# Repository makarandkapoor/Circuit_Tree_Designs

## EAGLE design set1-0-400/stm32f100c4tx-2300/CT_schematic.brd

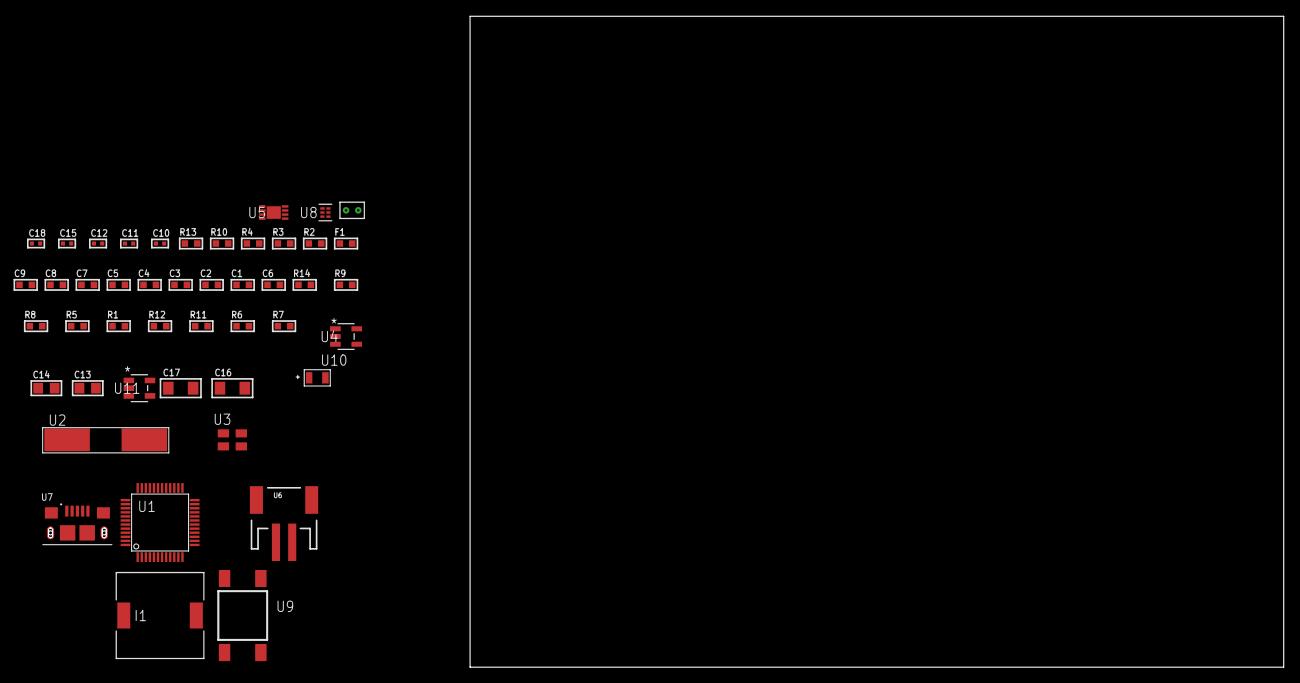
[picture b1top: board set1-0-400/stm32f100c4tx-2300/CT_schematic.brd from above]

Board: 2 copper layers, 151.8 x 80.0 mm, 46 parts (0 on the bottom side), 22 nets, no tracks yet.

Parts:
C1, C9: 1e-06; C0603
C2, C3, C4, C5: 1e-07; C0603
C6: 4.7e-06; C0603
C7, C8: 1e-08; C0603
C10, C11: 1e-11; C0402
C12, C18: 1e-08; C0402
C13, C14: 1e-05; C0805
C15: 1e-07; C0402
C16, C17: 1e-05; C1206
F1: 240.0; L0603
I1: 2.5e-06; DR1040
R1, R5, R8, R9, R14: 10000.0; R0603
R2: 1000.0; R0603
R3: 1600.5; R0603
R4: 4700.0; R0603
R6: 220000.0; R0603
R7: 1000000.0; R0603
R10: 9100.0; R0603
R11: 680000.0; R0603
R12: 120000.0; R0603
R13: 2000.0; R0603
U1: stm32f100c4t6; LQFP48
U2: ABLS-25.000MHZ-B2F-T
U3: ASEK-32.768KHz-ECST; ASEK
U4: ltc3406es5; TSOT-23-5
U5: MCP73831T-2ACI/MC; DFN8_2X3MC
U6: S2B-PH-SM4-TB(LF)(SN); JST-2-SMD
U7: 10118193-0001LF; FCI_10118193-0001LF
U8: TPS3895ADRYR; SON-6
U9: 4-1437565-2; SW_4-1437565-2
U10: Q65110A2395; LGM67K-G1J2-24-Z
U11: nc7sz125m5x; NC7SZ125M5X
U12: Dummy; DUMMY_PACKAGE_92

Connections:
CLK_CRYSTAL_U1_5: C10.1, U1.5, U2.1
CLK_CRYSTAL_U1_6: C11.1, U1.6, U2.2
CLK_U1_3: U1.3, U3.3
GND: C1.2, C2.2, C3.2, C4.2, C5.2, C6.2, C7.2, C8.2, C9.2, C10.2, C11.2, C12.2, C13.2, C14.1, C14.2, C15.2, C16.2, C17.2, C18.2, R2.2, R5.2, R6.2, R10.2, R12.2, R13.2, U1.8, U1.23, U1.35, U1.47, U3.2, U4.2, U5.6, U5.9, U6.2, U7.5, U7.6, U7.7, U7.8, U7.9, U8.2, U10.C, U11.1, U11.3, U12.1
INPUT_USBPOWER_5V: C16.1, R14.2, U5.1, U5.2, U7.1
NET_U1_7: R4.1, U1.7, U11.4
NET_U1_9: C7.1, C8.1, C9.1, F1.1, U1.9
NET_U1_44: R5.1, U1.44
NET_U1_45: R3.1, U1.45, U10.A
NET_U1_46: R1.1, U1.46, U9.3, U9.4
NET_U4_3: I1.1, U4.3
NET_U4_5: R6.1, R7.1, U4.5
NET_U4_ATNET_3: I1.2, R7.2
NET_U5_5: R14.1, U5.5
NET_U5_8: R13.1, U5.8
NET_U8_1: R9.1, R10.1, U8.1
NET_U8_3: R11.2, R12.1, U8.3
NET_U8_4: R8.1, U8.4, U11.2
NET_U9_1: R2.1, U9.1, U9.2
PROC_DAC_OUT2: U1.15, U12.2
VCC_S1_3V7: C13.1, C17.1, U4.4, U5.3, U5.4, U6.1
VCC_TIER1_3V3: C1.1, C2.1, C3.1, C4.1, C5.1, C6.1, C12.1, C14.2, C15.1, C18.1, F1.2, I1.2, R1.2, R3.2, R4.2, R7.2, R8.2, R9.2, R11.1, U1.1, U1.24, U1.36, U1.48, U3.4, U8.6, U11.5

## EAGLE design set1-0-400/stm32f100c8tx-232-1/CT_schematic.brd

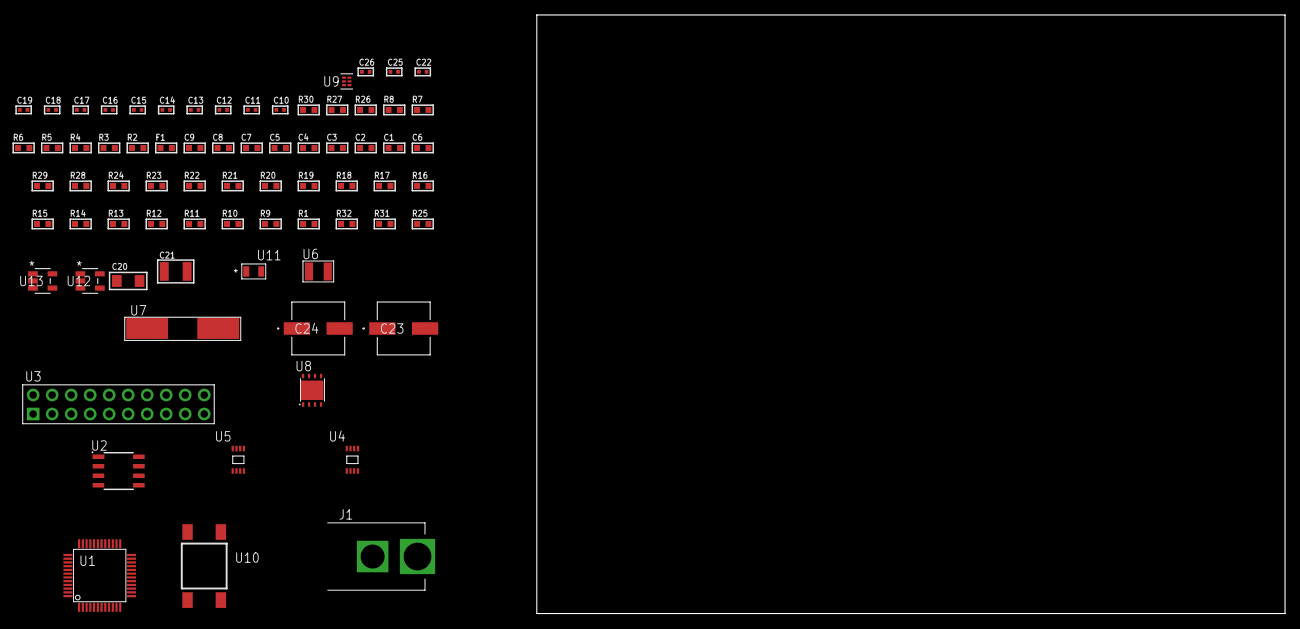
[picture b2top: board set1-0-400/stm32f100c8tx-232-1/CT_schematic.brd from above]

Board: 2 copper layers, 100.0 x 80.0 mm, 73 parts (0 on the bottom side), 42 nets, no tracks yet.

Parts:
C1, C9: 1e-06; C0603
C2, C3, C4, C5: 1e-07; C0603
C6: 4.7e-06; C0603
C7, C8: 1e-08; C0603
C10, C11, C12, C13: 1e-11; C0402
C14, C17, C18, C19, C25, C26: 1e-08; C0402
C15, C16, C22: 1e-07; C0402
C20: 1e-05; C1206
C21: 1e-05; C1210
C23, C24: 0.0001; EXV-9H
F1: 240.0; L0603
J1: PJ-037B; PJ-037B_PACKAGE
R1, R9, R10, R11, R12, R13, R14, R15, R16, R17, R18, R19, R20, R21, R22, R23, R24, R28, R29: 10000.0; R0603
R2, R27: 1000.0; R0603
R3: 1600.5; R0603
R4: 4700.0; R0603
R5, R6, R7, R8: 2200.0; R0603
R25: 100000.0; R0603
R26: 2231.0; R0603
R30: 9100.0; R0603
R31: 680000.0; R0603
R32: 120000.0; R0603
U1: stm32f100c8t7; LQFP48
U2: AT25020B-SSHL-T; SOIC-8
U3: TST-110-05-T-D-RA
U4, U5: 24AA128T-I/MNY; TDFN-8/6MM
U6: ABS07-32.768KHZ-7-T
U7: ABLS-25.000MHZ-B2F-T
U8: LP3878SDX-ADJ/NOPB; WSON-8
U9: TPS3895ADRYR; SON-6
U10: 4-1437565-2; SW_4-1437565-2
U11: Q65110A2395; LGM67K-G1J2-24-Z
U12, U13: nc7sz125m5x; NC7SZ125M5X

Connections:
CLK_CRYSTAL_U1_3: C10.1, U1.3, U6.1
CLK_CRYSTAL_U1_4: C11.1, U1.4, U6.2
CLK_CRYSTAL_U1_5: C12.1, U1.5, U7.1
CLK_CRYSTAL_U1_6: C13.1, U1.6, U7.2
GND: C1.2, C2.2, C3.2, C4.2, C5.2, C6.2, C7.2, C8.2, C9.2, C10.2, C11.2, C12.2, C13.2, C14.2, C15.2, C16.2, C17.2, C18.2, C19.2, C20.2, C21.2, C22.2, C23.2, C24.2, C25.2, C26.2, J1.2, R2.2, R9.2, R18.2, R20.2, R21.2, R23.2, R27.2, R30.2, R32.2, U1.8, U1.23, U1.35, U1.47, U2.4, U3.4, U3.6, U3.8, U3.10, U3.12, U3.14, U3.16, U3.18, U3.20, U4.4, U4.7, U5.4, U5.7, U8.3, U8.PAD, U9.2, U11.C, U12.2, U12.3, U13.1, U13.3
NET_U1_7: R4.1, U1.7, U13.4
NET_U1_9: C7.1, C8.1, C9.1, F1.1, U1.9
NET_U1_21: R7.1, U1.21, U5.6
NET_U1_22: R8.1, U1.22, U5.5
NET_U1_42: R5.1, U1.42, U4.6
NET_U1_43: R6.1, U1.43, U4.5
NET_U1_44: R9.1, U1.44
NET_U1_45: R3.1, U1.45, U11.A
NET_U1_46: R1.1, U1.46, U10.3, U10.4
NET_U2_3: R10.1, U2.3
NET_U2_7: R12.1, U2.7
NET_U3_3: R13.1, U3.3
NET_U3_7: R15.1, U3.7
NET_U3_9: R16.1, U3.9
NET_U3_19: R18.1, U3.19
NET_U4_1: R19.1, U4.1
NET_U4_2: R20.1, U4.2
NET_U4_3: R21.1, U4.3
NET_U5_1: R22.1, U5.1
NET_U5_2: R23.1, U5.2
NET_U5_3: R24.1, U5.3
NET_U8_1: C19.1, U8.1
NET_U8_6: R26.2, R27.1, U8.6
NET_U8_8: R25.1, U8.8
NET_U9_1: R29.1, R30.1, U9.1
NET_U9_3: R31.2, R32.1, U9.3
NET_U9_4: R28.1, U9.4, U12.4, U13.2
NET_U10_1: R2.1, U10.1, U10.2
PROC_SPI1_MISO: U1.16, U2.2
PROC_SPI1_MOSI: U1.17, U2.5
PROC_SPI1_NSS: R11.1, U1.14, U2.1
PROC_SPI1_SCK: U1.15, U2.6
PROC_SYS_JTDI: R14.1, U1.38, U3.5
PROC_SYS_JTDO_TRACESWO: U1.39, U3.13
RST_OUT_U3_SRESET_B: R17.1, U3.15, U12.1
VCC_S1_6V4: C20.1, C23.1, C24.1, J1.1, R25.2, U8.4
VCC_TIER1_3V3: C1.1, C2.1, C3.1, C4.1, C5.1, C6.1, C14.1, C15.1, C16.1, C17.1, C18.1, C21.1, C22.1, C25.1, C26.1, F1.2, R1.2, R3.2, R4.2, R5.2, R6.2, R7.2, R8.2, R10.2, R11.2, R12.2, R13.2, R14.2, R15.2, R16.2, R17.2, R19.2, R22.2, R24.2, R26.1, R28.2, R29.2, R31.1, U1.1, U1.24, U1.36, U1.48, U2.8, U3.1, U3.2, U4.8, U5.8, U8.5, U9.6, U12.5, U13.5

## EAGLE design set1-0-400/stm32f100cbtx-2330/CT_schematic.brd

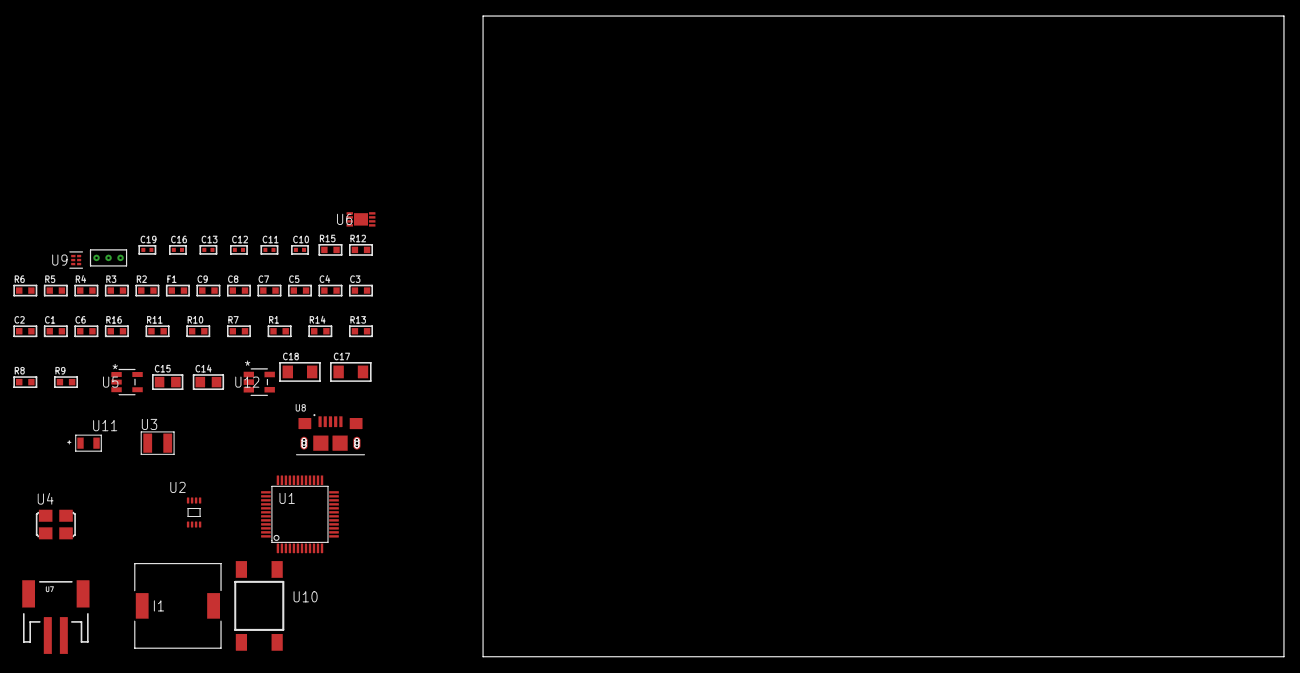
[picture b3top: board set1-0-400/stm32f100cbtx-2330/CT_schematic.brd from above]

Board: 2 copper layers, 122.6 x 80.0 mm, 50 parts (0 on the bottom side), 25 nets, no tracks yet.

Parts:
C1, C9: 1e-06; C0603
C2, C3, C4, C5: 1e-07; C0603
C6: 4.7e-06; C0603
C7, C8: 1e-08; C0603
C10, C11: 1e-11; C0402
C12, C13, C19: 1e-08; C0402
C14, C15: 1e-05; C0805
C16: 1e-07; C0402
C17, C18: 1e-05; C1206
F1: 240.0; L0603
I1: 2.5e-06; DR1040
R1, R7, R10, R11, R16: 10000.0; R0603
R2: 1000.0; R0603
R3: 1600.5; R0603
R4: 4700.0; R0603
R5, R6: 2200.0; R0603
R8: 220000.0; R0603
R9: 1000000.0; R0603
R12: 9100.0; R0603
R13: 680000.0; R0603
R14: 120000.0; R0603
R15: 2000.0; R0603
U1: stm32f100cbt7; LQFP48
U2: 24AA04-I/MC; TDFN-8/6MM
U3: ABS07-32.768KHZ-7-T
U4: ASFL1-25MHZ-NCS; ASFL1
U5: ltc3406es5; TSOT-23-5
U6: MCP73831T-2ACI/MC; DFN8_2X3MC
U7: S2B-PH-SM4-TB(LF)(SN); JST-2-SMD
U8: 10118193-0001LF; FCI_10118193-0001LF
U9: TPS3895ADRYR; SON-6
U10: 4-1437565-2; SW_4-1437565-2
U11: Q65110A2395; LGM67K-G1J2-24-Z
U12: nc7sz125m5x; NC7SZ125M5X
U13: Dummy; DUMMY_PACKAGE_103

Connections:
CLK_CRYSTAL_U1_3: C10.1, U1.3, U3.1
CLK_CRYSTAL_U1_4: C11.1, U1.4, U3.2
CLK_U1_5: U1.5, U4.3
GND: C1.2, C2.2, C3.2, C4.2, C5.2, C6.2, C7.2, C8.2, C9.2, C10.2, C11.2, C12.2, C13.2, C14.2, C15.1, C15.2, C16.2, C17.2, C18.2, C19.2, R2.2, R7.2, R8.2, R12.2, R14.2, R15.2, U1.8, U1.23, U1.35, U1.47, U2.4, U2.7, U4.2, U5.2, U6.6, U6.9, U7.2, U8.5, U8.6, U8.7, U8.8, U8.9, U9.2, U11.C, U12.1, U12.3, U13.1
INPUT_USBPOWER_5V: C17.1, R16.2, U6.1, U6.2, U8.1
NET_U1_7: R4.1, U1.7, U12.4
NET_U1_9: C7.1, C8.1, C9.1, F1.1, U1.9
NET_U1_42: R5.1, U1.42, U2.6
NET_U1_43: R6.1, U1.43, U2.5
NET_U1_44: R7.1, U1.44
NET_U1_45: R3.1, U1.45, U11.A
NET_U1_46: R1.1, U1.46, U10.3, U10.4
NET_U5_3: I1.1, U5.3
NET_U5_5: R8.1, R9.1, U5.5
NET_U5_ATNET_3: I1.2, R9.2
NET_U6_5: R16.1, U6.5
NET_U6_8: R15.1, U6.8
NET_U9_1: R11.1, R12.1, U9.1
NET_U9_3: R13.2, R14.1, U9.3
NET_U9_4: R10.1, U9.4, U12.2
NET_U10_1: R2.1, U10.1, U10.2
PROC_PC13_TAMPER_RTC: U1.2, U13.2
PROC_PD1_OSC_OUT: U1.6, U13.3
VCC_S1_3V7: C14.1, C18.1, U5.4, U6.3, U6.4, U7.1
VCC_TIER1_3V3: C1.1, C2.1, C3.1, C4.1, C5.1, C6.1, C12.1, C13.1, C15.2, C16.1, C19.1, F1.2, I1.2, R1.2, R3.2, R4.2, R5.2, R6.2, R9.2, R10.2, R11.2, R13.1, U1.1, U1.24, U1.36, U1.48, U2.8, U4.4, U9.6, U12.5

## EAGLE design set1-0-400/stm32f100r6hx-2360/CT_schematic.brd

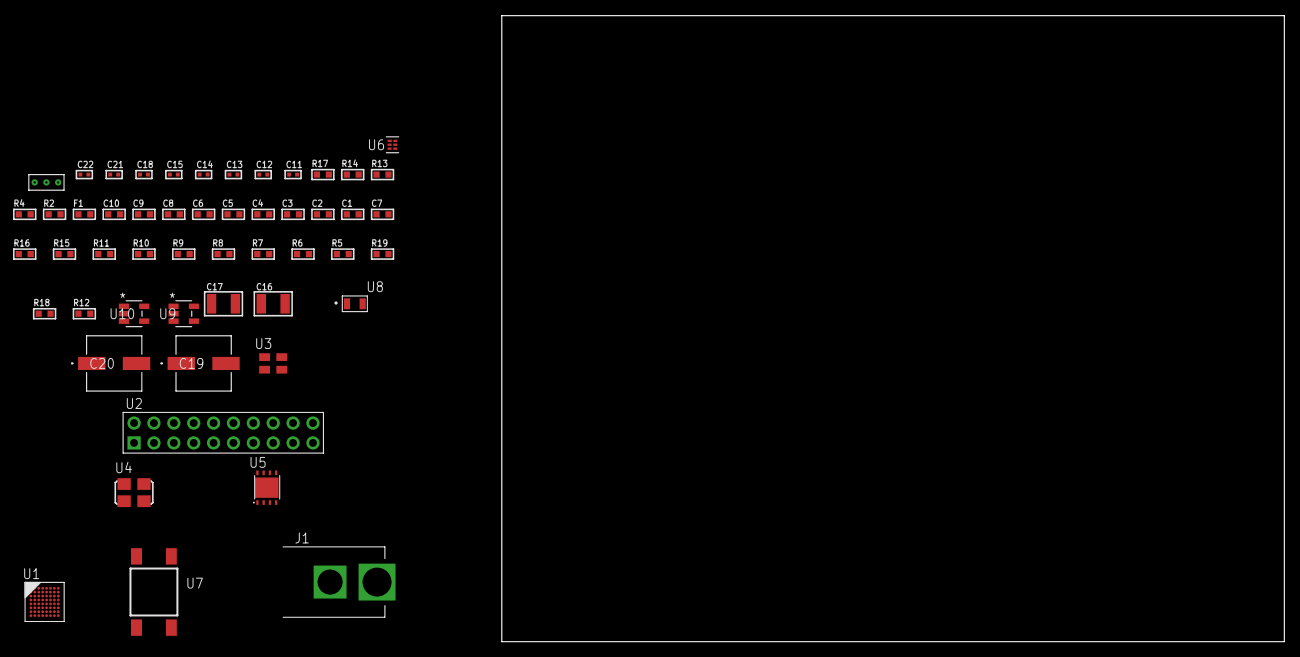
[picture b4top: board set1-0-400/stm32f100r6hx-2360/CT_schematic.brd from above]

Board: 2 copper layers, 100.0 x 80.0 mm, 52 parts (0 on the bottom side), 25 nets, no tracks yet.

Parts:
C1, C10: 1e-06; C0603
C2, C3, C4, C5, C6: 1e-07; C0603
C7: 4.7e-06; C0603
C8, C9: 1e-08; C0603
C11, C12, C18: 1e-07; C0402
C13, C14, C15, C21, C22: 1e-08; C0402
C16, C17: 1e-05; C1210
C19, C20: 0.0001; EXV-9H
F1: 240.0; L0603
J1: PJ-037B; PJ-037B_PACKAGE
R2, R14: 1000.0; R0603
R4: 4700.0; R0603
R5, R6, R7, R8, R9, R10, R11, R15, R16: 10000.0; R0603
R12: 100000.0; R0603
R13: 2231.0; R0603
R17: 9100.0; R0603
R18: 680000.0; R0603
R19: 120000.0; R0603
U1: stm32f100r6h6; TFBGA64
U2: TST-110-05-T-D-RA
U3: ASEK-32.768KHz-ECST; ASEK
U4: ASFL1-25MHZ-NCS; ASFL1
U5: LP3878SDX-ADJ/NOPB; WSON-8
U6: TPS3895ADRYR; SON-6
U7: 4-1437565-2; SW_4-1437565-2
U8: Q65110A2395; LGM67K-G1J2-24-Z
U9, U10: nc7sz125m5x; NC7SZ125M5X
U11: Dummy; DUMMY_PACKAGE_110

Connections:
CLK_U1_A1: U1.A1, U3.3
CLK_U1_C1: U1.C1, U4.3
GND: C1.2, C2.2, C3.2, C4.2, C5.2, C6.2, C7.2, C8.2, C9.2, C10.2, C11.2, C12.2, C13.2, C14.2, C15.2, C16.2, C17.2, C18.2, C19.2, C20.2, C21.2, C22.2, J1.2, R2.2, R5.2, R11.2, R14.2, R17.2, R19.2, U1.C2, U1.D4, U1.D5, U1.D6, U1.F1, U2.4, U2.6, U2.8, U2.10, U2.12, U2.14, U2.16, U2.18, U2.20, U3.2, U4.2, U5.3, U5.PAD, U6.2, U8.C, U9.2, U9.3, U10.1, U10.3, U11.1
NET_U1_B4: R5.1, U1.B4
NET_U1_E1: R4.1, U1.E1, U10.4
NET_U1_H1: C8.1, C9.1, C10.1, F1.1, U1.G1, U1.H1
NET_U1_H8: U7.3, U7.4
NET_U2_3: R6.1, U2.3
NET_U2_7: R8.1, U2.7
NET_U2_9: R9.1, U2.9
NET_U2_19: R11.1, U2.19
NET_U5_1: C15.1, U5.1
NET_U5_6: R13.2, R14.1, U5.6
NET_U5_8: R12.1, U5.8
NET_U6_1: R16.1, R17.1, U6.1
NET_U6_3: R18.2, R19.1, U6.3
NET_U6_4: R15.1, U6.4, U9.4, U10.2
NET_U7_1: R2.1, U7.1, U7.2
PROC_SYS_JTDI: R7.1, U1.A6, U2.5
PROC_SYS_JTDO_TRACESWO: U1.A5, U2.13
PROC_TIM1_CH2: U1.C7, U11.3
PROC_TIM1_CH4: U1.C8, U11.2
RST_OUT_U2_SRESET_B: R10.1, U2.15, U9.1
VCC_S1_15V8: C16.1, C19.1, C20.1, J1.1, R12.2, U5.4
VCC_TIER1_3V3: C1.1, C2.1, C3.1, C4.1, C5.1, C6.1, C7.1, C11.1, C12.1, C13.1, C14.1, C17.1, C18.1, C21.1, C22.1, F1.2, R4.2, R6.2, R7.2, R8.2, R9.2, R10.2, R13.1, R15.2, R16.2, R18.1, U1.B2, U1.D2, U1.E4, U1.E5, U1.E6, U2.1, U2.2, U3.4, U4.4, U5.5, U6.6, U9.5, U10.5

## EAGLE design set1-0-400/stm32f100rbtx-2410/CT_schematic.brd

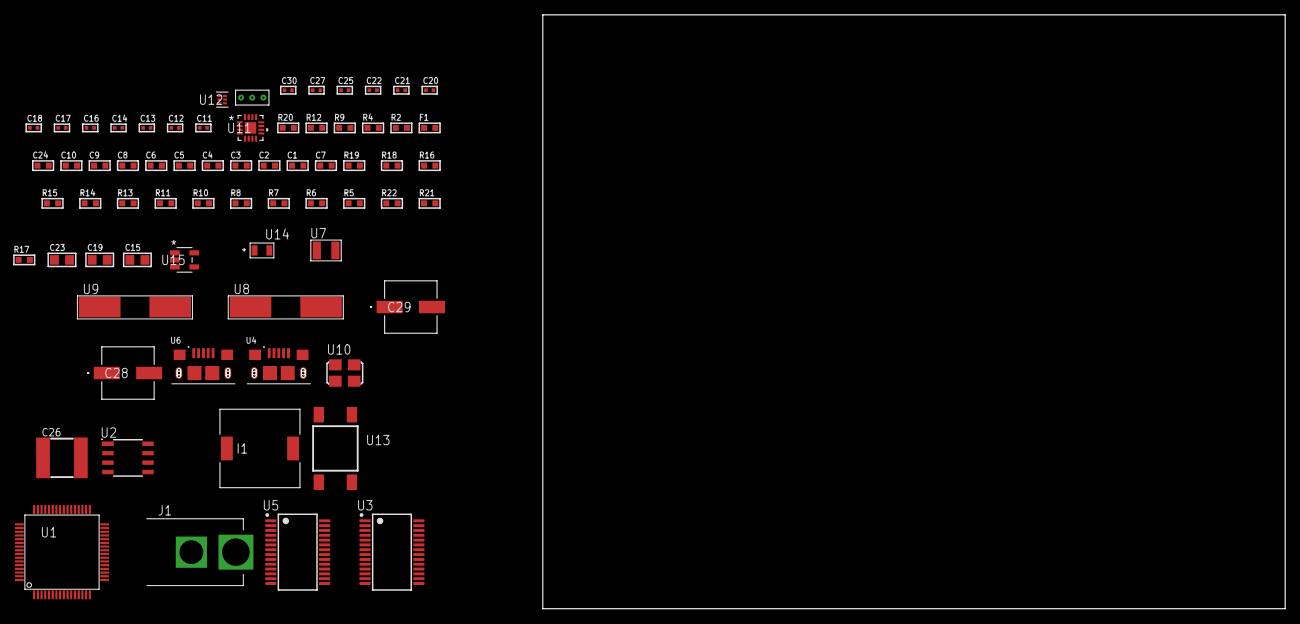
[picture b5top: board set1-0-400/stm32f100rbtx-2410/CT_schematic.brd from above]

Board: 2 copper layers, 69 parts (0 on the bottom side), 52 nets, no tracks yet.

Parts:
C1, C10, C24: 1e-06; C0603
C2, C3, C4, C5, C6: 1e-07; C0603
C7: 4.7e-06; C0603
C8, C9: 1e-08; C0603
C11, C12: 1e-11; C0402
C13, C22, C30: 1e-08; C0402
C14, C16, C17, C18, C20, C21, C25, C27: 1e-07; C0402
C15, C19: 4.7e-06; C0805
C23: 1e-05; C0805
C26: 6.8e-05; 2220
C28, C29: 0.0001; EXV-9H
F1: 240.0; L0603
I1: 3.8e-06; DR1040
J1: PJ-037B; PJ-037B_PACKAGE
R2: 1000.0; R0603
R4, R9, R12: 4700.0; R0603
R5, R6, R7, R8, R10, R11, R13, R14, R18, R19: 10000.0; R0603
R15: 20000.0; R0603
R16: 91000.0; R0603
R17: 300000.0; R0603
R20: 9100.0; R0603
R21: 680000.0; R0603
R22: 120000.0; R0603
U1: stm32f100rbt7; LQFP64
U2: AT25080B-SSHL-T; SOIC-8
U3, U5: FT232RL-REEL; SSOP-28
U4, U6: 10118193-0001LF; FCI_10118193-0001LF
U7: ABS07-32.768KHZ-7-T
U8, U9: ABLS-12.000MHZ-B4-T
U10: ASFL1-25MHZ-NCS; ASFL1
U11: LTC3601EUD#PBF; QFN-16_EP
U12: TPS3895ADRYR; SON-6
U13: 4-1437565-2; SW_4-1437565-2
U14: Q65110A2395; LGM67K-G1J2-24-Z
U15: nc7sz125m5x; NC7SZ125M5X
U16: Dummy; DUMMY_PACKAGE_143

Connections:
CLK_CRYSTAL_U1_3: C11.1, U1.3, U7.1
CLK_CRYSTAL_U1_4: C12.1, U1.4, U7.2
CLK_CRYSTAL_U3_27: U3.27, U8.1
CLK_CRYSTAL_U3_28: U3.28, U8.2
CLK_CRYSTAL_U5_27: U5.27, U9.1
CLK_CRYSTAL_U5_28: U5.28, U9.2
CLK_U1_5: U1.5, U10.3
GND: C1.2, C2.2, C3.2, C4.2, C5.2, C6.2, C7.2, C8.2, C9.2, C10.2, C11.2, C12.2, C13.2, C14.2, C15.2, C16.2, C17.2, C18.2, C19.2, C20.2, C21.2, C22.2, C23.2, C24.2, C26.1, C26.2, C27.2, C28.2, C29.2, C30.2, J1.2, R2.2, R5.2, R11.2, R14.2, R15.2, R17.2, R20.2, R22.2, U1.12, U1.18, U1.31, U1.47, U1.63, U2.4, U3.7, U3.18, U3.21, U3.25, U3.26, U4.5, U4.6, U4.7, U4.8, U4.9, U5.7, U5.18, U5.21, U5.25, U5.26, U6.5, U6.6, U6.7, U6.8, U6.9, U10.2, U11.1, U11.9, U11.17, U12.2, U14.C, U15.1, U15.3, U16.1
NET_U1_7: R4.1, U1.7, U15.4
NET_U1_13: C8.1, C9.1, C10.1, F1.1, U1.13
NET_U1_60: R5.1, U1.60
NET_U1_62: U13.3, U13.4
NET_U2_3: R6.1, U2.3
NET_U2_7: R8.1, U2.7
NET_U3_14: R10.1, U3.14
NET_U3_17: C16.1, U3.17
NET_U3_19: R11.1, U3.19
NET_U4_1: R9.1, U4.1
NET_U4_2: U3.16, U4.2
NET_U4_3: U3.15, U4.3
NET_U5_14: R13.1, U5.14
NET_U5_17: C20.1, U5.17
NET_U5_19: R14.1, U5.19
NET_U6_1: R12.1, U6.1
NET_U6_2: U5.16, U6.2
NET_U6_3: U5.15, U6.3
NET_U11_3: C25.2, I1.1, U11.3, U11.4
NET_U11_6: C25.1, U11.6
NET_U11_7: C24.1, U11.7, U11.12
NET_U11_10: R17.1, U11.10
NET_U11_11: R15.1, R16.1, U11.11
NET_U11_ATNET_3: I1.2, R16.2
NET_U12_1: R19.1, R20.1, U12.1
NET_U12_3: R21.2, R22.1, U12.3
NET_U12_4: R18.1, U12.4, U15.2
NET_U13_1: R2.1, U13.1, U13.2
PROC_PC13_TAMPER_RTC: U1.2, U16.2
PROC_PD1_OSC_OUT: U1.6, U16.3
PROC_SPI1_MISO: U1.22, U2.2
PROC_SPI1_MOSI: U1.23, U2.5
PROC_SPI1_NSS: R7.1, U1.20, U2.1
PROC_SPI1_SCK: U1.21, U2.6
PROC_USART1_CTS: U1.44, U3.3
PROC_USART1_RTS: U1.45, U3.11
PROC_USART1_RX: U1.43, U3.1
PROC_USART1_TX: U1.42, U3.5
PROC_USART2_CTS: U1.14, U5.3
PROC_USART2_RTS: U1.15, U5.11
PROC_USART2_RX: U1.17, U5.1
PROC_USART2_TX: U1.16, U5.5
VCC_S1_6V0: C23.1, C28.1, C29.1, J1.1, U11.15, U11.16
VCC_TIER1_3V3: C1.1, C2.1, C3.1, C4.1, C5.1, C6.1, C7.1, C13.1, C14.1, C15.1, C17.1, C18.1, C19.1, C21.1, C22.1, C26.2, C27.1, C30.1, F1.2, I1.2, R4.2, R6.2, R7.2, R8.2, R10.2, R13.2, R16.2, R18.2, R19.2, R21.1, U1.1, U1.19, U1.32, U1.48, U1.64, U2.8, U3.4, U3.20, U5.4, U5.20, U10.4, U11.8, U12.6, U15.5

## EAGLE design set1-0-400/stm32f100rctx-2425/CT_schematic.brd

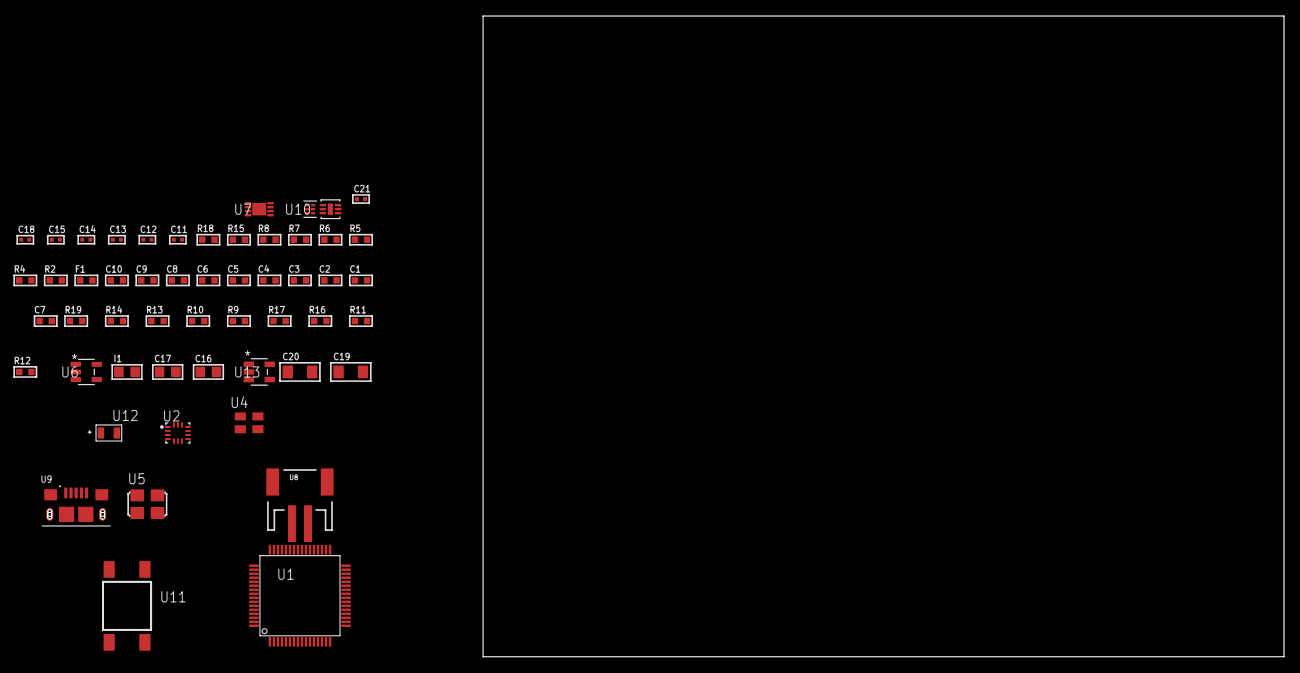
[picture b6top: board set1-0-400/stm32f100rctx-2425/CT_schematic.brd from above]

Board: 2 copper layers, 154.3 x 80.0 mm, 53 parts (0 on the bottom side), 25 nets, no tracks yet.

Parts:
C1, C10: 1e-06; C0603
C2, C3, C4, C5, C6: 1e-07; C0603
C7: 4.7e-06; C0603
C8, C9: 1e-08; C0603
C11, C12, C13, C18: 1e-07; C0402
C14, C15, C21: 1e-08; C0402
C16, C17: 1e-05; C0805
C19, C20: 1e-05; C1206
F1: 240.0; L0603
I1: 2.2e-06; L0805
R2: 1000.0; R0603
R4: 4700.0; R0603
R5, R6, R7, R8: 2200.0; R0603
R9, R10, R13, R14, R19: 10000.0; R0603
R11: 220000.0; R0603
R12: 1000000.0; R0603
R15: 9100.0; R0603
R16: 680000.0; R0603
R17: 120000.0; R0603
R18: 2000.0; R0603
U1: stm32f100rct7; LQFP64
U2: BMG250; LGA-14
U3: SI7006-A20-IM; DFN-6
U4: ASEK-32.768KHz-ECST; ASEK
U5: ASFL1-25MHZ-NCS; ASFL1
U6: ltc3406es5; TSOT-23-5
U7: MCP73831T-2ACI/MC; DFN8_2X3MC
U8: S2B-PH-SM4-TB(LF)(SN); JST-2-SMD
U9: 10118193-0001LF; FCI_10118193-0001LF
U10: TPS3895ADRYR; SON-6
U11: 4-1437565-2; SW_4-1437565-2
U12: Q65110A2395; LGM67K-G1J2-24-Z
U13: nc7sz125m5x; NC7SZ125M5X

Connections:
CLK_U1_3: U1.3, U4.3
CLK_U1_5: U1.5, U5.3
GND: C1.2, C2.2, C3.2, C4.2, C5.2, C6.2, C7.2, C8.2, C9.2, C10.2, C11.2, C12.2, C13.2, C14.2, C15.2, C16.2, C17.1, C17.2, C18.2, C19.2, C20.2, C21.2, R2.2, R9.2, R11.2, R15.2, R17.2, R18.2, U1.12, U1.18, U1.31, U1.47, U1.63, U2.1, U2.6, U2.7, U3.2, U3.7, U4.2, U5.2, U6.2, U7.6, U7.9, U8.2, U9.5, U9.6, U9.7, U9.8, U9.9, U10.2, U12.C, U13.1, U13.3
INPUT_USBPOWER_5V: C19.1, R19.2, U7.1, U7.2, U9.1
NET_U1_7: R4.1, U1.7, U13.4
NET_U1_13: C8.1, C9.1, C10.1, F1.1, U1.13
NET_U1_29: R7.1, U1.29, U2.13
NET_U1_30: R8.1, U1.30, U2.14
NET_U1_58: R5.1, U1.58, U3.6
NET_U1_59: R6.1, U1.59, U3.1
NET_U1_60: R9.1, U1.60
NET_U1_62: U11.3, U11.4
NET_U2_12: R10.1, U2.12
NET_U6_3: I1.1, U6.3
NET_U6_5: R11.1, R12.1, U6.5
NET_U6_ATNET_3: I1.2, R12.2
NET_U7_5: R19.1, U7.5
NET_U7_8: R18.1, U7.8
NET_U10_1: R14.1, R15.1, U10.1
NET_U10_3: R16.2, R17.1, U10.3
NET_U10_4: R13.1, U10.4, U13.2
NET_U11_1: R2.1, U11.1, U11.2
PROC_GPIO_TO_U2_INT1: U1.2, U2.4
VCC_S1_3V7: C16.1, C20.1, U6.4, U7.3, U7.4, U8.1
VCC_TIER1_3V3: C1.1, C2.1, C3.1, C4.1, C5.1, C6.1, C7.1, C11.1, C12.1, C13.1, C14.1, C15.1, C17.2, C18.1, C21.1, F1.2, I1.2, R4.2, R5.2, R6.2, R7.2, R8.2, R10.2, R12.2, R13.2, R14.2, R16.1, U1.1, U1.19, U1.32, U1.48, U1.64, U2.5, U2.8, U3.5, U4.4, U5.4, U10.6, U13.5

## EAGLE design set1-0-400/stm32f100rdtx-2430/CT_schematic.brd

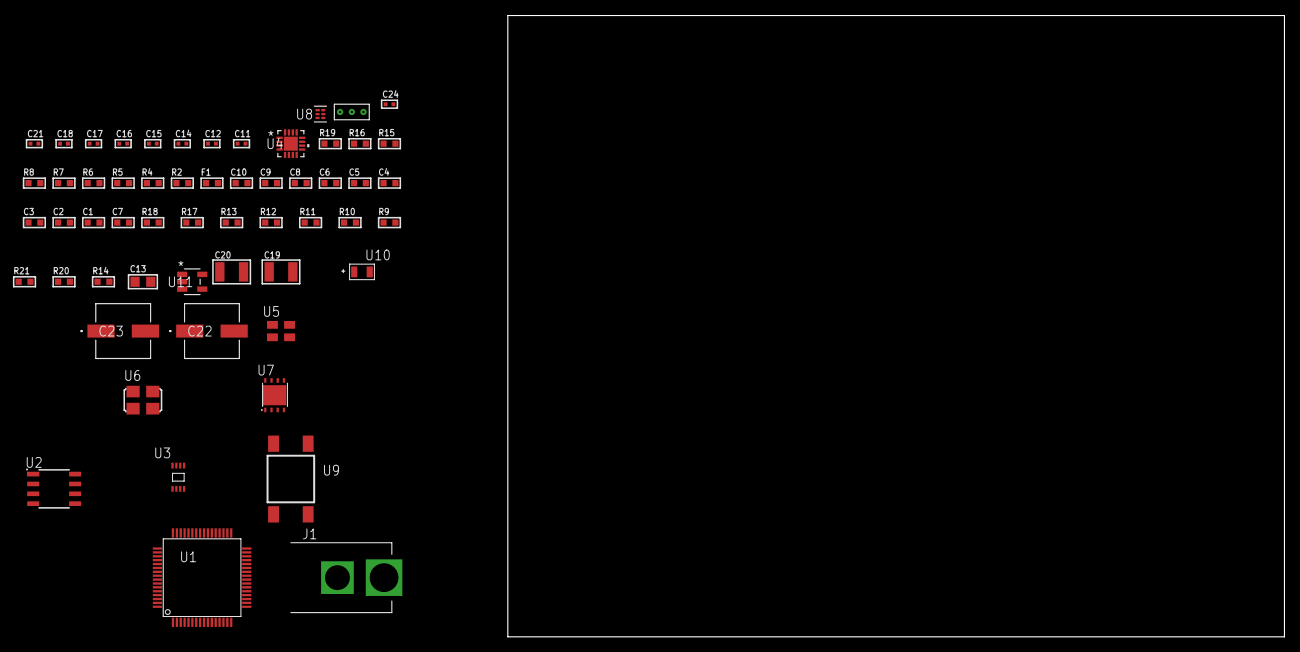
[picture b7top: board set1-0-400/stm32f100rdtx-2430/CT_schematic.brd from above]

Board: 2 copper layers, 100.0 x 80.0 mm, 57 parts (0 on the bottom side), 30 nets, no tracks yet.

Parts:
C1, C10: 1e-06; C0603
C2, C3, C4, C5, C6: 1e-07; C0603
C7: 4.7e-06; C0603
C8, C9: 1e-08; C0603
C11, C12, C16, C17, C18, C24: 1e-08; C0402
C13: 4.7e-06; C0805
C14, C15, C21: 1e-07; C0402
C19, C20: 1e-05; C1210
C22, C23: 0.0001; EXV-9H
F1: 240.0; L0603
J1: PJ-037B; PJ-037B_PACKAGE
R2, R16: 1000.0; R0603
R4: 4700.0; R0603
R5, R6, R7, R8: 2200.0; R0603
R9, R10, R11, R12, R13, R17, R18: 10000.0; R0603
R14: 100000.0; R0603
R15: 2231.0; R0603
R19: 9100.0; R0603
R20: 680000.0; R0603
R21: 120000.0; R0603
U1: stm32f100rdt6; LQFP64
U2: AT25080B-SSHL-T; SOIC-8
U3: 24AA02T-I/MNY; TDFN-8/6MM
U4: MMA8451QT; QFN-16
U5: ASEK-32.768KHz-ECST; ASEK
U6: ASFL1-25MHZ-NCS; ASFL1
U7: LP3878SDX-ADJ/NOPB; WSON-8
U8: TPS3895ADRYR; SON-6
U9: 4-1437565-2; SW_4-1437565-2
U10: Q65110A2395; LGM67K-G1J2-24-Z
U11: nc7sz125m5x; NC7SZ125M5X
U12: Dummy; DUMMY_PACKAGE_126

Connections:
CLK_U1_3: U1.3, U5.3
CLK_U1_5: U1.5, U6.3
GND: C1.2, C2.2, C3.2, C4.2, C5.2, C6.2, C7.2, C8.2, C9.2, C10.2, C11.2, C12.2, C13.2, C14.2, C15.2, C16.2, C17.2, C18.2, C19.2, C20.2, C21.2, C22.2, C23.2, C24.2, J1.2, R2.2, R9.2, R16.2, R19.2, R21.2, U1.12, U1.18, U1.31, U1.47, U1.63, U2.4, U3.4, U4.5, U4.10, U4.12, U4.17, U5.2, U6.2, U7.3, U7.PAD, U8.2, U10.C, U11.1, U11.3, U12.1
NET_U1_7: R4.1, U1.7, U11.4
NET_U1_13: C8.1, C9.1, C10.1, F1.1, U1.13
NET_U1_29: R7.1, U1.29, U3.6
NET_U1_30: R8.1, U1.30, U3.5
NET_U1_58: R5.1, U1.58, U4.4
NET_U1_59: R6.1, U1.59, U4.6
NET_U1_60: R9.1, U1.60
NET_U1_62: U9.3, U9.4
NET_U2_3: R10.1, U2.3
NET_U2_7: R12.1, U2.7
NET_U4_2: C15.1, U4.2
NET_U4_7: R13.1, U4.7
NET_U7_1: C18.1, U7.1
NET_U7_6: R15.2, R16.1, U7.6
NET_U7_8: R14.1, U7.8
NET_U8_1: R18.1, R19.1, U8.1
NET_U8_3: R20.2, R21.1, U8.3
NET_U8_4: R17.1, U8.4, U11.2
NET_U9_1: R2.1, U9.1, U9.2
PROC_SPI1_MISO: U1.22, U2.2
PROC_SPI1_MOSI: U1.23, U2.5
PROC_SPI1_NSS: R11.1, U1.20, U2.1
PROC_SPI1_SCK: U1.21, U2.6
PROC_TIM1_CH2: U1.42, U12.2
PROC_TIM1_CH4: U1.44, U12.3
VCC_S1_14V9: C19.1, C22.1, C23.1, J1.1, R14.2, U7.4
VCC_TIER1_3V3: C1.1, C2.1, C3.1, C4.1, C5.1, C6.1, C7.1, C11.1, C12.1, C13.1, C14.1, C16.1, C17.1, C20.1, C21.1, C24.1, F1.2, R4.2, R5.2, R6.2, R7.2, R8.2, R10.2, R11.2, R12.2, R13.2, R15.1, R17.2, R18.2, R20.1, U1.1, U1.19, U1.32, U1.48, U1.64, U2.8, U3.7, U3.8, U4.1, U4.14, U5.4, U6.4, U7.5, U8.6, U11.5
